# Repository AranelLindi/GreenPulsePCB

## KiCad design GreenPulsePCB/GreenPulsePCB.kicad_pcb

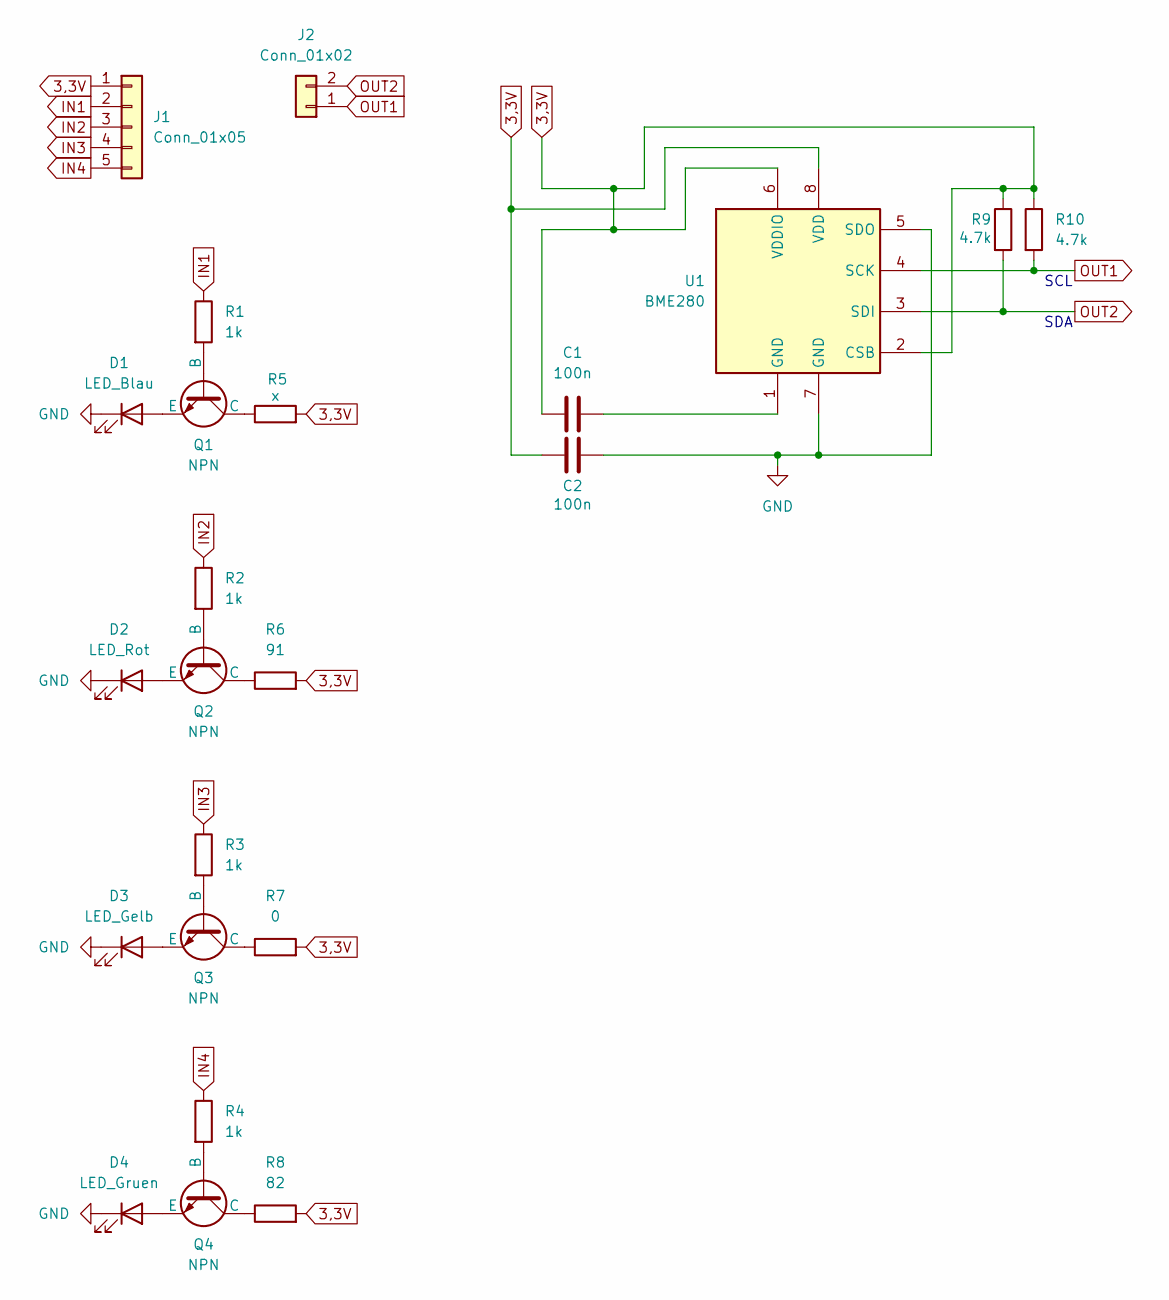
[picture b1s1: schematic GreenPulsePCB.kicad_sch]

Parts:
C1, C2: 100n; C_0805_2012Metric
D1: LED_Blau; LED_0805_2012Metric
D2: LED_Rot; LED_0805_2012Metric
D3: LED_Gelb; LED_0805_2012Metric
D4: LED_Gruen; LED_0805_2012Metric
J1: Conn_01x05; PinSocket_1x05_P2.54mm_Horizontal
J2: Conn_01x02; PinSocket_1x02_P2.54mm_Horizontal
Q1, Q2, Q3, Q4: NPN; SOT-23
R1, R2, R3, R4: 1k; R_0805_2012Metric
R5: x; R_0805_2012Metric
R6: 91; R_0805_2012Metric
R7: 0; R_0805_2012Metric
R8: 82; R_0805_2012Metric
R9, R10: 4.7k; R_0805_2012Metric
U1: BME280; Bosch_LGA-8_2.5x2.5mm_P0.65mm_ClockwisePinNumbering

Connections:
3,3V: C1.2, C2.1, J1.1, R5.2, R6.2, R7.2, R8.2, R9.1, R10.1, U1.2 (CSB), U1.6 (VDDIO), U1.8 (VDD)
GND: C2.2, D1.1 (K), D2.1 (K), D3.1 (K), D4.1 (K), U1.5 (SDO), U1.7 (GND)
IN1: J1.2, R1.1
IN2: J1.3, R2.1
IN3: J1.4, R3.1
IN4: J1.5, R4.1
unnamed: C1.1, U1.1 (GND)
unnamed: D1.2 (A), Q1.3 (E)
unnamed: D2.2 (A), Q2.3 (E)
unnamed: D3.2 (A), Q3.3 (E)
unnamed: D4.2 (A), Q4.3 (E)
unnamed: Q1.2 (B), R1.2
unnamed: Q1.1 (C), R5.1
unnamed: Q2.2 (B), R2.2
unnamed: Q2.1 (C), R6.1
unnamed: Q3.2 (B), R3.2
unnamed: Q3.1 (C), R7.1
unnamed: Q4.2 (B), R4.2
unnamed: Q4.1 (C), R8.1
OUT1: J2.1, R10.2, U1.4 (SCK)
OUT2: J2.2, R9.2, U1.3 (SDI)

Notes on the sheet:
SCL
SDA

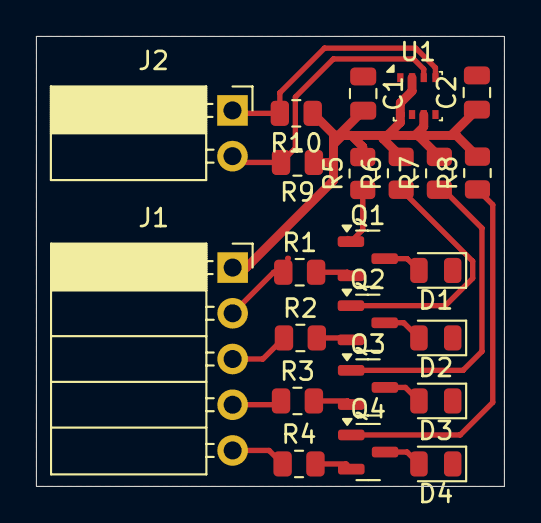
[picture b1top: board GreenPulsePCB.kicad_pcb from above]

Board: 2 copper layers, 26.0 x 25.0 mm, 23 parts (0 on the bottom side), 21 nets.

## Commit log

2024-12-25 BME280 integrated
    BME280 Sensor finally integrated as shown in sensor's datasheet (p. 39)
2025-01-22 LEDs added
    LEDs added (inc. data sheets and hyperlinks) as well as schematics view (screenshot)
2025-01-24 Schaltplan fertiggestellt
    Transistoren hinzugefügt um Schaltung der LEDs zu ermöglichen. Vorwiderstände der LEDs müssen noch berechnet werden. Auch Schaltung des BME280 nochmal überprüfen.
2025-01-24 Footprints zugewiesen
    Allen Bauteilen ihre Footprints zugewiesen.
2025-01-24 Platzierung vorläufig abgeschlossen
    Noch auf Plausibilität / kürzeste Pfade prüfen. Routen der Pfade ist noch nicht erfolgt!
2025-01-25 Routing abgeschlossen
    Kann trotzdem noch Fehler beinhalten. Nochmal gründlich überprüfen!
